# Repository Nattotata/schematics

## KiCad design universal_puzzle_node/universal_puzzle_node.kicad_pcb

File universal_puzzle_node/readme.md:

## useful links

- pinout and discussion on arduino [forum](https://forum.arduino.cc/t/esp32-c3-supermini-pinout/1189850)
- wifi debugging on arduino [forum](https://forum.arduino.cc/t/no-wifi-connect-with-esp32-c3-super-mini/1324046/25)
- potential replacement (same chip, different board) [seeedstudio wiki](https://wiki.seeedstudio.com/XIAO_ESP32C3_Getting_Started/)

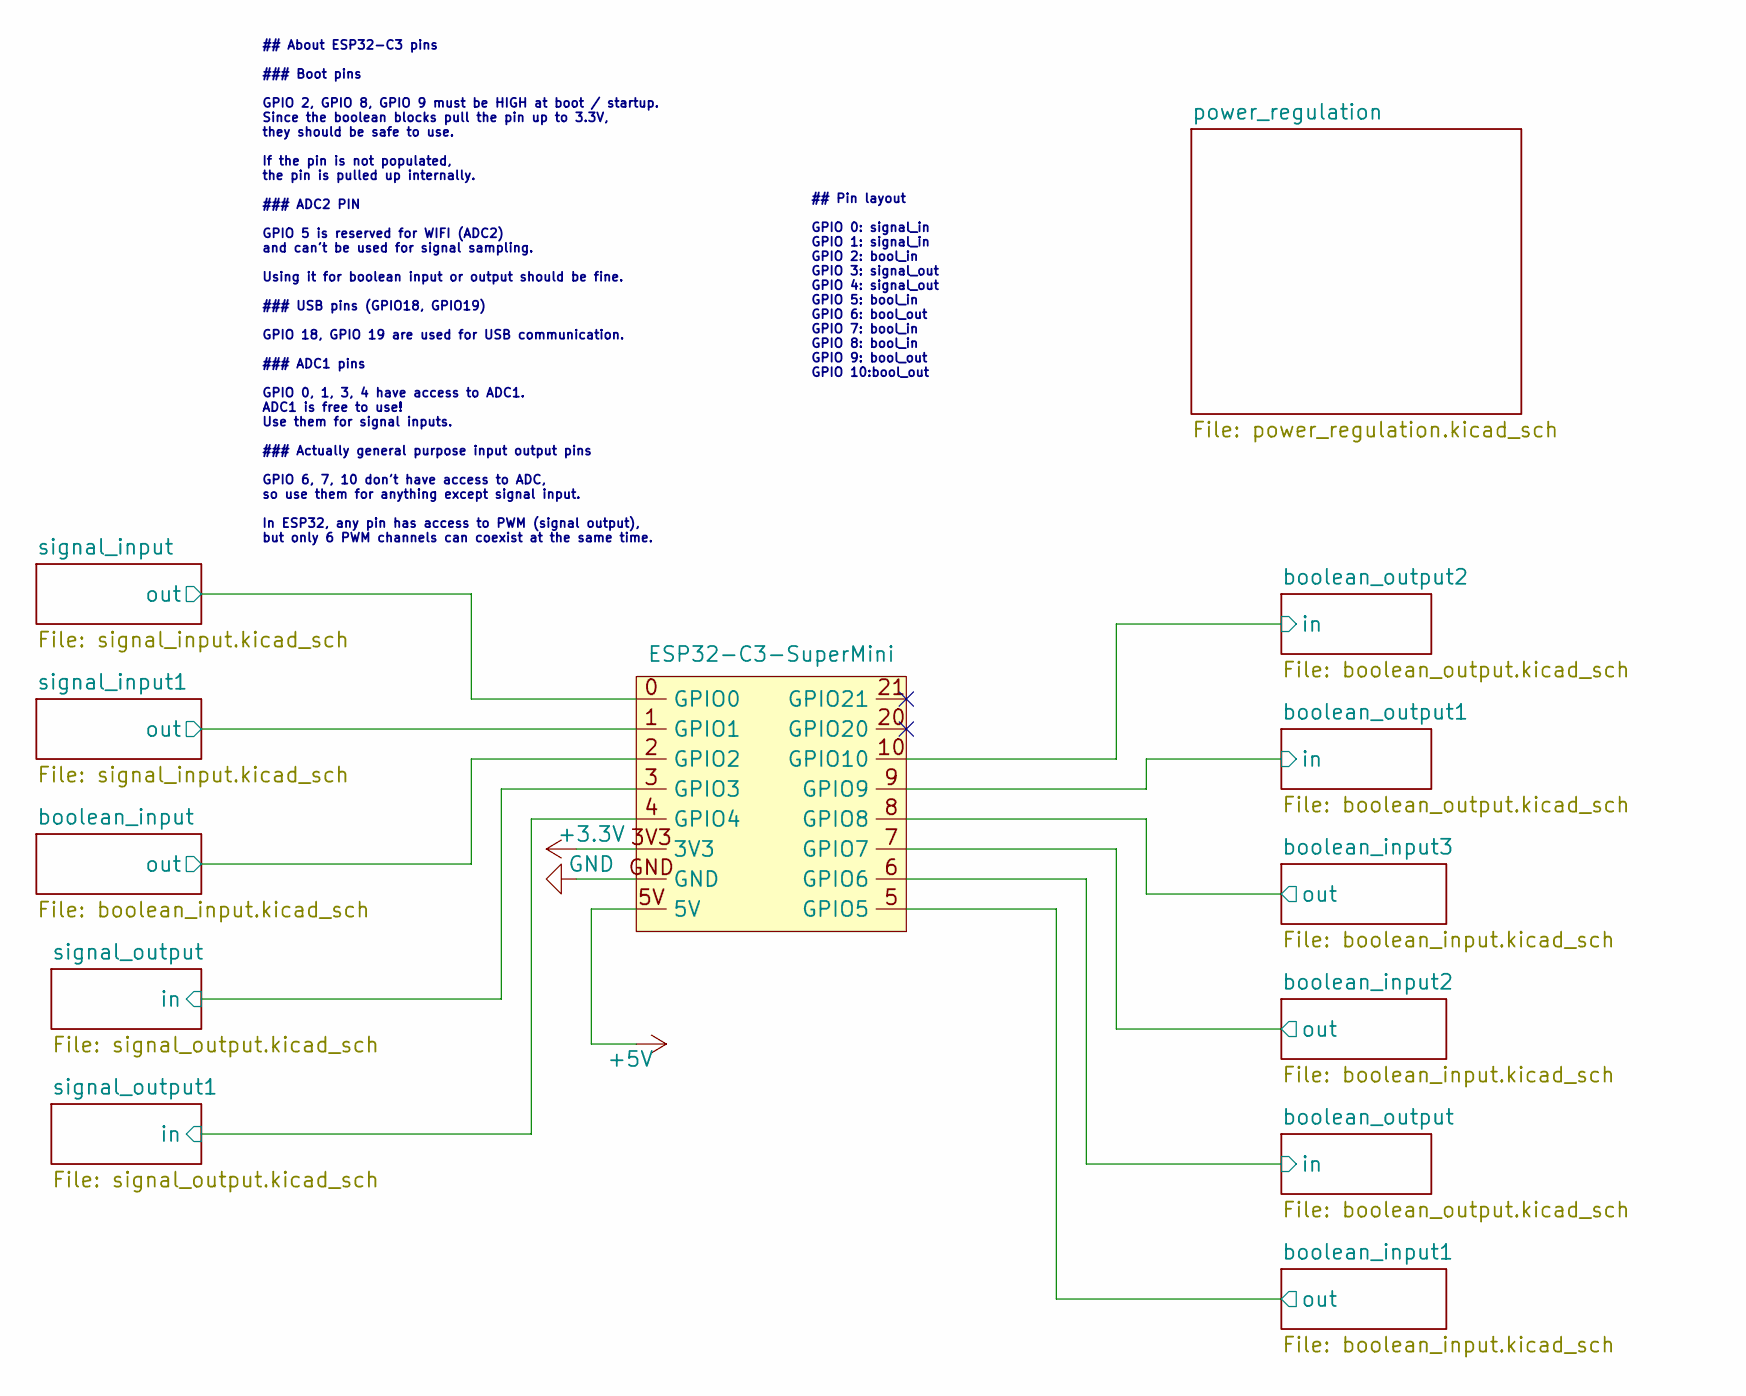
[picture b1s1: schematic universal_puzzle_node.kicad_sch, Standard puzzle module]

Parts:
U1: ESP32-C3-SuperMini

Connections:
+3.3V: U1.3V3; also elsewhere on the board
+5V: U1.5V; also elsewhere on the board
/boolean_input1/out: U1.5 (GPIO5); also elsewhere on the board
/boolean_input2/out: U1.7 (GPIO7); also elsewhere on the board
/boolean_input3/out: U1.8 (GPIO8); also elsewhere on the board
/boolean_input/out: U1.2 (GPIO2); also elsewhere on the board
/boolean_output1/in: U1.9 (GPIO9); also elsewhere on the board
/boolean_output2/in: U1.10 (GPIO10); also elsewhere on the board
/boolean_output/in: U1.6 (GPIO6); also elsewhere on the board
/signal_input1/out: U1.1 (GPIO1); also elsewhere on the board
/signal_input/out: U1.0 (GPIO0); also elsewhere on the board
/signal_output1/in: U1.4 (GPIO4); also elsewhere on the board
/signal_output/in: U1.3 (GPIO3); also elsewhere on the board
GND: U1.GND; also elsewhere on the board

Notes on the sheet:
## About ESP32-C3 pins ### Boot pins GPIO 2, GPIO 8, GPIO 9 must be HIGH at boot / startup. Since the boolean blocks pull the pin up to 3.3V, they should be safe to use. If the pin is not populated, the pin is pulled up internally. ### ADC2 PIN GPIO 5 is reserved for WIFI (ADC2) and can't be used f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
## Pin layout GPIO 0: signal_in GPIO 1: signal_in GPIO 2: bool_in GPIO 3: signal_out GPIO 4: signal_out GPIO 5: bool_in GPIO 6: bool_out GPIO 7: bool_in GPIO 8: bool_in GPIO 9: bool_out GPIO 10:bool_out

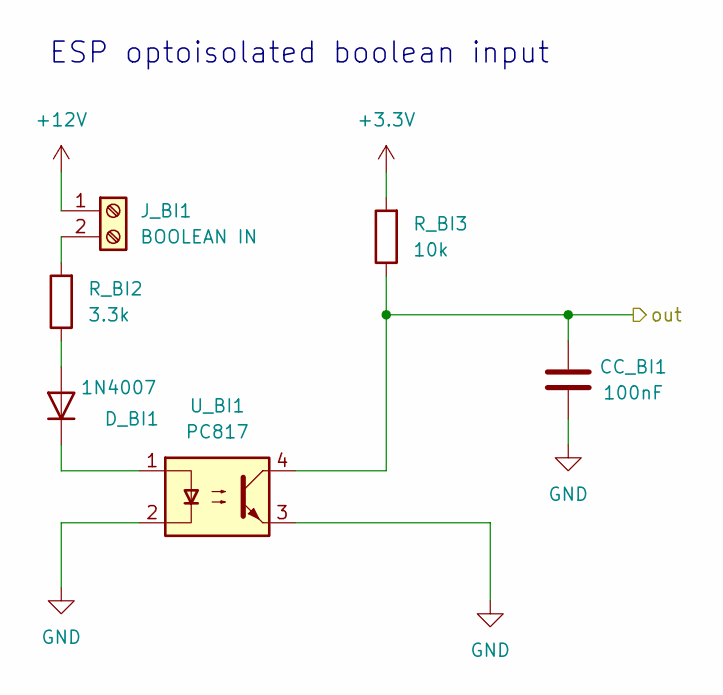
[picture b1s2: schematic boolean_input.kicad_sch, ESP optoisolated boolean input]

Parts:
CC_BI1: 100nF; C_Disc_D5.0mm_W2.5mm_P5.00mm
D_BI1: 1N4007; D_DO-41_SOD81_P10.16mm_Horizontal
J_BI1: BOOLEAN IN; TerminalBlock_Phoenix_MKDS-1,5-2-5.08_1x02_P5.08mm_Horizont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
R_BI2: 3.3k; R_Axial_DIN0207_L6.3mm_D2.5mm_P10.16mm_Horizontal
R_BI3: 10k; R_Axial_DIN0207_L6.3mm_D2.5mm_P10.16mm_Horizontal
U_BI1: PC817; DIP-4_W7.62mm

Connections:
+3.3V: R_BI3.2; also elsewhere on the board
+12V: J_BI1.1; also elsewhere on the board
/boolean_input/out: CC_BI1.1, R_BI3.1, U_BI1.4; also elsewhere on the board
GND: CC_BI1.2, U_BI1.2, U_BI1.3; also elsewhere on the board
unnamed: D_BI1.2 (A), R_BI2.1
unnamed: D_BI1.1 (K), U_BI1.1
unnamed: J_BI1.2, R_BI2.2

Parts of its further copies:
CC_BI2, CC_BI3, CC_BI4: 100nF; C_Disc_D5.0mm_W2.5mm_P5.00mm
D_BI2, D_BI3, D_BI4: 1N4007; D_DO-41_SOD81_P10.16mm_Horizontal
J_BI2, J_BI3, J_BI4: BOOLEAN IN; TerminalBlock_Phoenix_MKDS-1,5-2-5.08_1x02_P5.08mm_Horizont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
R_BI5, R_BI7, R_BI9: 3.3k; R_Axial_DIN0207_L6.3mm_D2.5mm_P10.16mm_Horizontal
R_BI6, R_BI8, R_BI10: 10k; R_Axial_DIN0207_L6.3mm_D2.5mm_P10.16mm_Horizontal
U_BI2, U_BI3, U_BI4: PC817; DIP-4_W7.62mm

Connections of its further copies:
+3.3V: R_BI6.2, R_BI8.2, R_BI10.2; also elsewhere on the board
+12V: J_BI2.1, J_BI3.1, J_BI4.1; also elsewhere on the board
/boolean_input1/out: CC_BI2.1, R_BI6.1, U_BI2.4; also elsewhere on the board
/boolean_input2/out: CC_BI3.1, R_BI8.1, U_BI3.4; also elsewhere on the board
/boolean_input3/out: CC_BI4.1, R_BI10.1, U_BI4.4; also elsewhere on the board
GND: CC_BI2.2, CC_BI3.2, CC_BI4.2, U_BI2.2, U_BI2.3, U_BI3.2, U_BI3.3, U_BI4.2, U_BI4.3; also elsewhere on the board
unnamed: D_BI2.2 (A), R_BI5.1
unnamed: D_BI2.1 (K), U_BI2.1
unnamed: D_BI3.2 (A), R_BI7.1
unnamed: D_BI3.1 (K), U_BI3.1
unnamed: D_BI4.2 (A), R_BI9.1
unnamed: D_BI4.1 (K), U_BI4.1
unnamed: J_BI2.2, R_BI5.2
unnamed: J_BI3.2, R_BI7.2
unnamed: J_BI4.2, R_BI9.2

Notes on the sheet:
ESP optoisolated boolean input

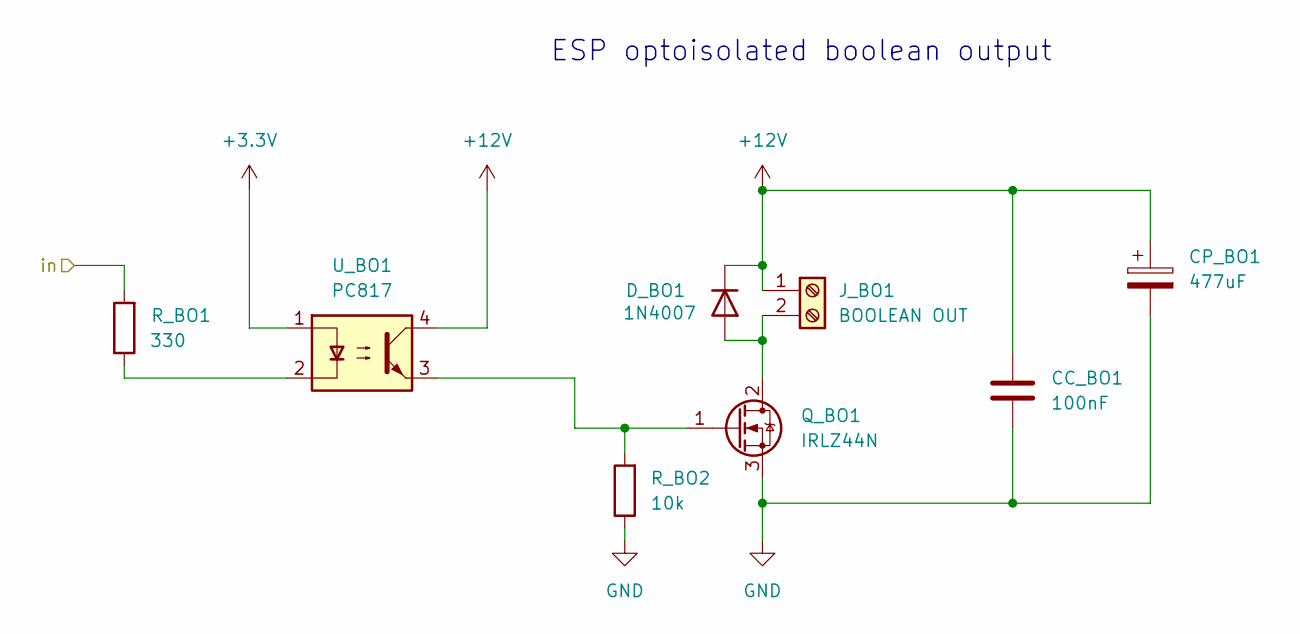
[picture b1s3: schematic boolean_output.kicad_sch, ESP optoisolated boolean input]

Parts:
CC_BO1: 100nF; C_Disc_D5.0mm_W2.5mm_P5.00mm
CP_BO1: 477uF; CP_Radial_D10.0mm_P5.00mm
D_BO1: 1N4007; D_DO-41_SOD81_P10.16mm_Horizontal
J_BO1: BOOLEAN OUT; TerminalBlock_Phoenix_MKDS-1,5-2-5.08_1x02_P5.08mm_Horizont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
Q_BO1: IRLZ44N; TO-220-3_Vertical
R_BO1: 330; R_Axial_DIN0207_L6.3mm_D2.5mm_P10.16mm_Horizontal
R_BO2: 10k; R_Axial_DIN0207_L6.3mm_D2.5mm_P10.16mm_Horizontal
U_BO1: PC817; DIP-4_W7.62mm

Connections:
+3.3V: U_BO1.1; also elsewhere on the board
+12V: CC_BO1.2, CP_BO1.1, D_BO1.1 (K), J_BO1.1, U_BO1.4; also elsewhere on the board
/boolean_output/in: R_BO1.2; also elsewhere on the board
GND: CC_BO1.1, CP_BO1.2, Q_BO1.3 (S), R_BO2.1; also elsewhere on the board
unnamed: D_BO1.2 (A), J_BO1.2, Q_BO1.2 (D)
unnamed: Q_BO1.1 (G), R_BO2.2, U_BO1.3
unnamed: R_BO1.1, U_BO1.2

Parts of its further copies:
CC_BO2, CC_BO3: 100nF; C_Disc_D5.0mm_W2.5mm_P5.00mm
CP_BO2, CP_BO3: 477uF; CP_Radial_D10.0mm_P5.00mm
D_BO2, D_BO3: 1N4007; D_DO-41_SOD81_P10.16mm_Horizontal
J_BO2, J_BO3: BOOLEAN OUT; TerminalBlock_Phoenix_MKDS-1,5-2-5.08_1x02_P5.08mm_Horizont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
Q_BO2, Q_BO3: IRLZ44N; TO-220-3_Vertical
R_BO3, R_BO5: 330; R_Axial_DIN0207_L6.3mm_D2.5mm_P10.16mm_Horizontal
R_BO4, R_BO6: 10k; R_Axial_DIN0207_L6.3mm_D2.5mm_P10.16mm_Horizontal
U_BO2, U_BO3: PC817; DIP-4_W7.62mm

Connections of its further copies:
+3.3V: U_BO2.1, U_BO3.1; also elsewhere on the board
+12V: CC_BO2.2, CC_BO3.2, CP_BO2.1, CP_BO3.1, D_BO2.1 (K), D_BO3.1 (K), J_BO2.1, J_BO3.1, U_BO2.4, U_BO3.4; also elsewhere on the board
/boolean_output1/in: R_BO3.2; also elsewhere on the board
/boolean_output2/in: R_BO5.2; also elsewhere on the board
GND: CC_BO2.1, CC_BO3.1, CP_BO2.2, CP_BO3.2, Q_BO2.3 (S), Q_BO3.3 (S), R_BO4.1, R_BO6.1; also elsewhere on the board
unnamed: D_BO2.2 (A), J_BO2.2, Q_BO2.2 (D)
unnamed: D_BO3.2 (A), J_BO3.2, Q_BO3.2 (D)
unnamed: Q_BO2.1 (G), R_BO4.2, U_BO2.3
unnamed: Q_BO3.1 (G), R_BO6.2, U_BO3.3
unnamed: R_BO3.1, U_BO2.2
unnamed: R_BO5.1, U_BO3.2

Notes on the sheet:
ESP optoisolated boolean output

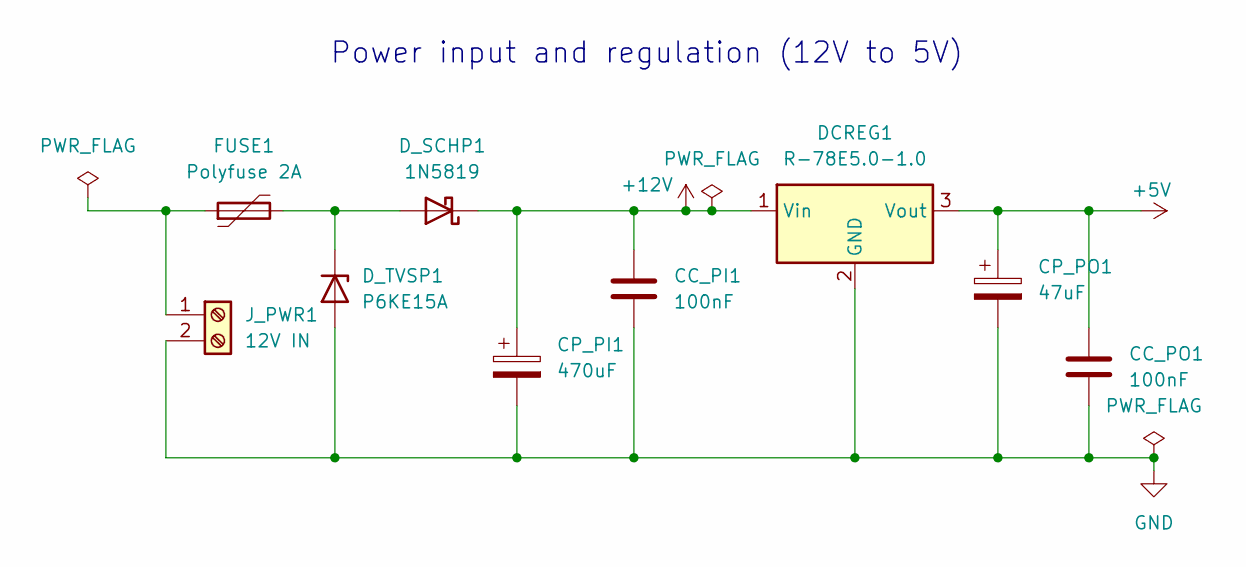
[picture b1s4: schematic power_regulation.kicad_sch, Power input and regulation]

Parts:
CC_PI1: 100nF; C_Disc_D5.0mm_W2.5mm_P5.00mm
CC_PO1: 100nF; C_Disc_D5.0mm_W2.5mm_P5.00mm
CP_PI1: 470uF; CP_Radial_D10.0mm_P5.00mm
CP_PO1: 47uF; CP_Radial_D6.3mm_P2.50mm
DCREG1: R-78E5.0-1.0; Converter_DCDC_RECOM_R-78E-0.5_THT
D_SCHP1: 1N5819; D_DO-35_SOD27_P7.62mm_Horizontal
D_TVSP1: P6KE15A; D_DO-15_P12.70mm_Horizontal
FUSE1: Polyfuse 2A; Fuse_BelFuse_0ZRE0040FF_L11.5mm_W3.8mm
J_PWR1: 12V IN; TerminalBlock_Phoenix_MKDS-1,5-2-5.08_1x02_P5.08mm_Horizont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

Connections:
+5V: CC_PO1.1, CP_PO1.1, DCREG1.3 (Vout); also elsewhere on the board
+12V: CC_PI1.1, CP_PI1.1, DCREG1.1 (Vin), D_SCHP1.1 (K); also elsewhere on the board
GND: CC_PI1.2, CC_PO1.2, CP_PI1.2, CP_PO1.2, DCREG1.2 (GND), D_TVSP1.2 (A), J_PWR1.2; also elsewhere on the board
unnamed: D_SCHP1.2 (A), D_TVSP1.1 (K), FUSE1.2
unnamed: FUSE1.1, J_PWR1.1

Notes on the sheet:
Power input and regulation (12V to 5V)

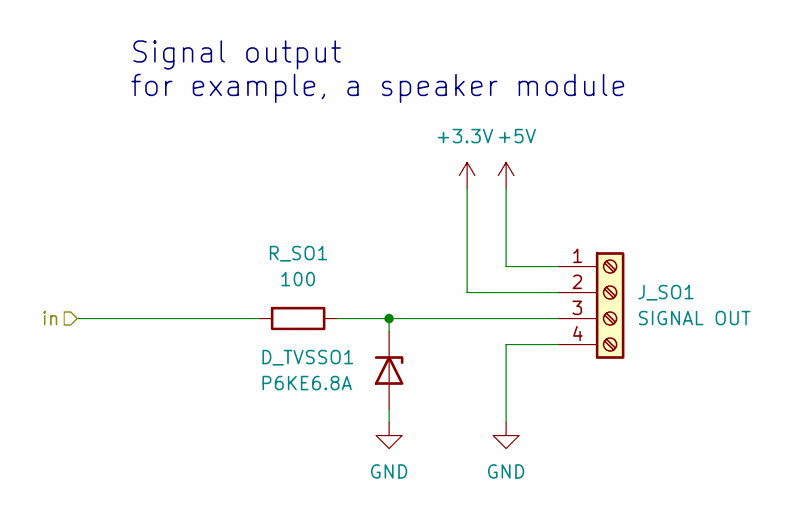
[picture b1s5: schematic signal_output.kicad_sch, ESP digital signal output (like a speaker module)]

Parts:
D_TVSSO1: P6KE6.8A; D_DO-15_P12.70mm_Horizontal
J_SO1: SIGNAL OUT; TerminalBlock_Phoenix_MKDS-1,5-4-5.08_1x04_P5.08mm_Horizont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
R_SO1: 100; R_Axial_DIN0207_L6.3mm_D2.5mm_P10.16mm_Horizontal

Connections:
+3.3V: J_SO1.2; also elsewhere on the board
+5V: J_SO1.1; also elsewhere on the board
/signal_output/in: R_SO1.2; also elsewhere on the board
GND: D_TVSSO1.2 (A), J_SO1.4; also elsewhere on the board
unnamed: D_TVSSO1.1 (K), J_SO1.3, R_SO1.1

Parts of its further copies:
D_TVSSO2: P6KE6.8A; D_DO-15_P12.70mm_Horizontal
J_SO2: SIGNAL OUT; TerminalBlock_Phoenix_MKDS-1,5-4-5.08_1x04_P5.08mm_Horizont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
R_SO4: 100; R_Axial_DIN0207_L6.3mm_D2.5mm_P10.16mm_Horizontal

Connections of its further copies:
+3.3V: J_SO2.2; also elsewhere on the board
+5V: J_SO2.1; also elsewhere on the board
/signal_output1/in: R_SO4.2; also elsewhere on the board
GND: D_TVSSO2.2 (A), J_SO2.4; also elsewhere on the board
unnamed: D_TVSSO2.1 (K), J_SO2.3, R_SO4.1

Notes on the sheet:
Signal output for example, a speaker module

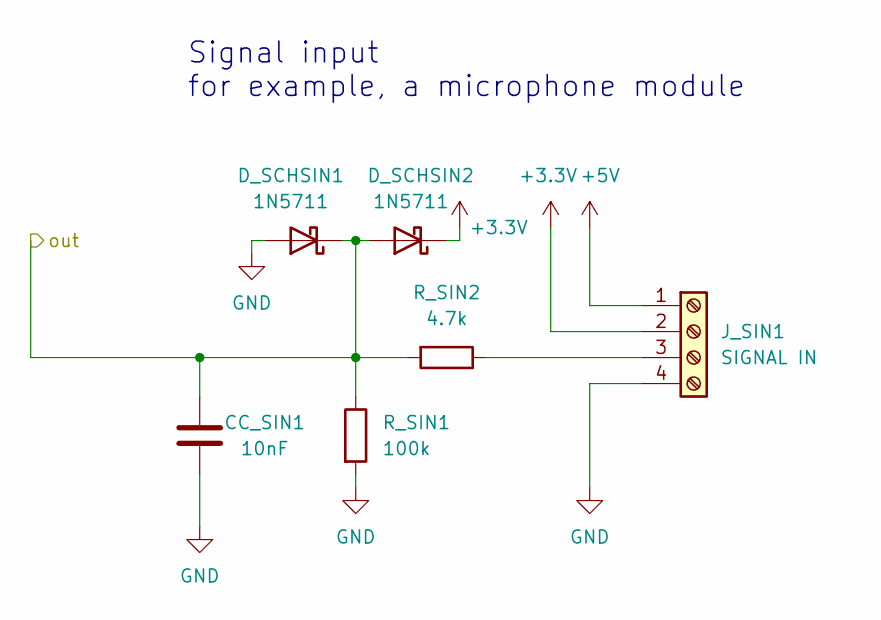
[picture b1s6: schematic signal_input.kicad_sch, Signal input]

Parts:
CC_SIN1: 10nF; C_Disc_D5.0mm_W2.5mm_P5.00mm
D_SCHSIN1, D_SCHSIN2: 1N5711; D_DO-35_SOD27_P7.62mm_Horizontal
J_SIN1: SIGNAL IN; TerminalBlock_Phoenix_MKDS-1,5-4-5.08_1x04_P5.08mm_Horizont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
R_SIN1: 100k; R_Axial_DIN0207_L6.3mm_D2.5mm_P10.16mm_Horizontal
R_SIN2: 4.7k; R_Axial_DIN0207_L6.3mm_D2.5mm_P10.16mm_Horizontal

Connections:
+3.3V: D_SCHSIN2.1 (K), J_SIN1.2; also elsewhere on the board
+5V: J_SIN1.1; also elsewhere on the board
/signal_input/out: CC_SIN1.1, R_SIN1.1, R_SIN2.2; also elsewhere on the board
GND: CC_SIN1.2, D_SCHSIN1.2 (A), J_SIN1.4, R_SIN1.2; also elsewhere on the board
unnamed: J_SIN1.3, R_SIN2.1

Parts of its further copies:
CC_SIN2: 10nF; C_Disc_D5.0mm_W2.5mm_P5.00mm
J_SIN2: SIGNAL IN; TerminalBlock_Phoenix_MKDS-1,5-4-5.08_1x04_P5.08mm_Horizont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
R_SIN3: 100k; R_Axial_DIN0207_L6.3mm_D2.5mm_P10.16mm_Horizontal
R_SIN4: 4.7k; R_Axial_DIN0207_L6.3mm_D2.5mm_P10.16mm_Horizontal

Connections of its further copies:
+3.3V: J_SIN2.2; also elsewhere on the board
+5V: J_SIN2.1; also elsewhere on the board
/signal_input1/out: CC_SIN2.1, R_SIN3.1, R_SIN4.2; also elsewhere on the board
GND: CC_SIN2.2, J_SIN2.4, R_SIN3.2; also elsewhere on the board
unnamed: J_SIN2.3, R_SIN4.1

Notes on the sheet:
Signal input for example, a microphone module

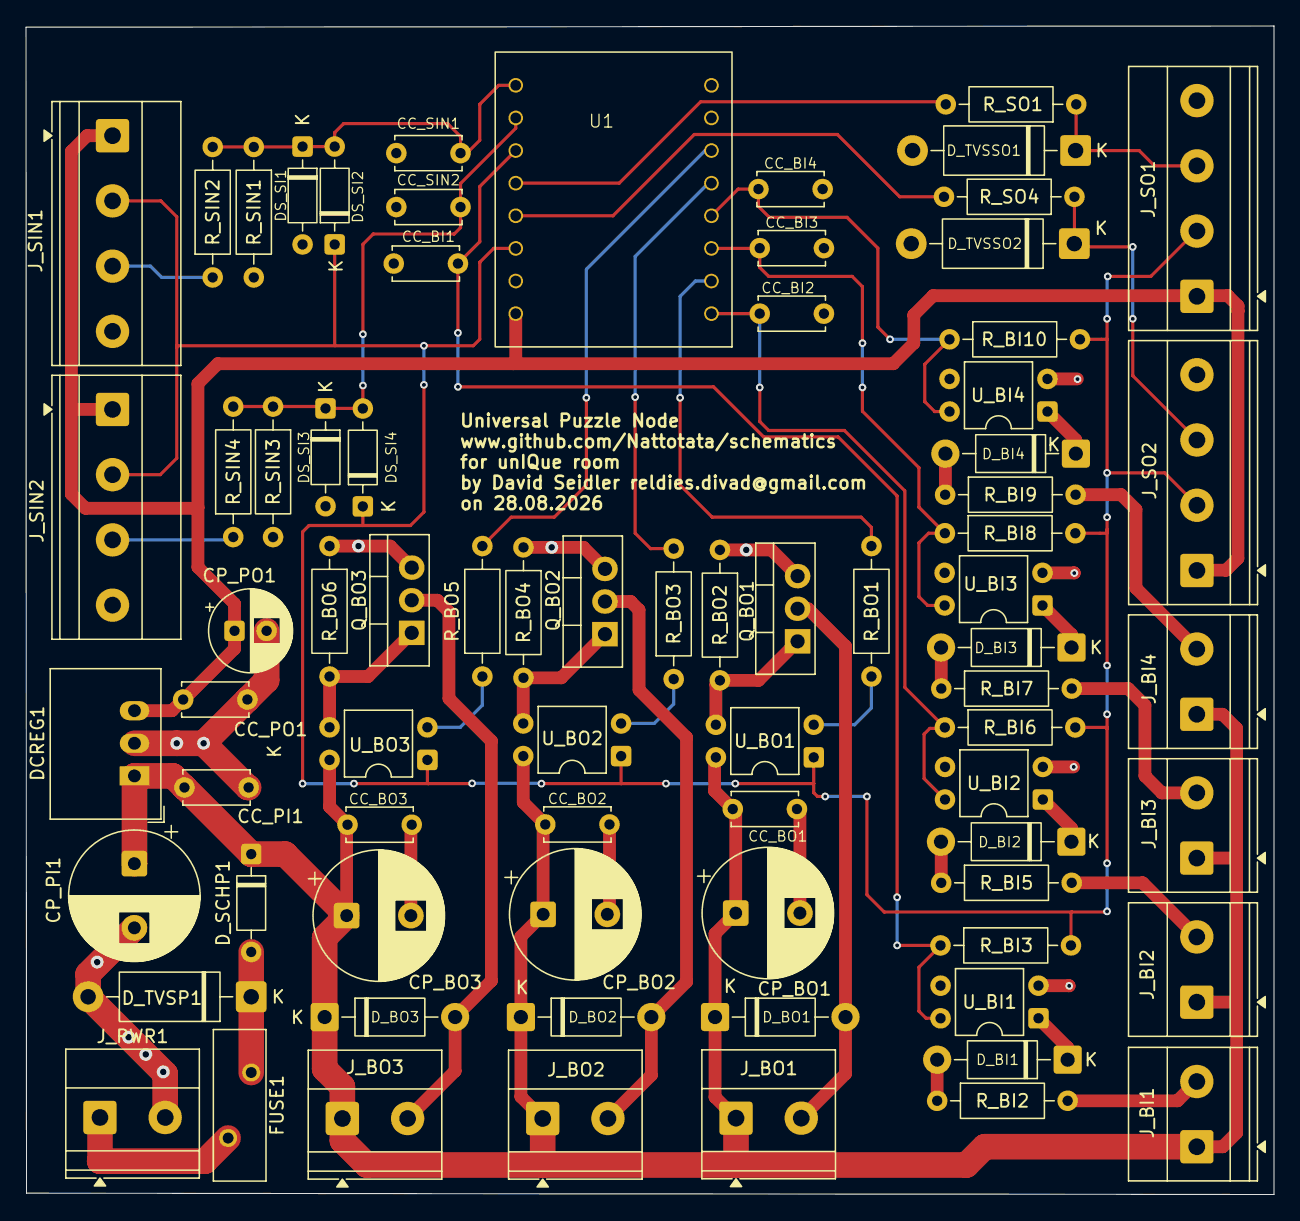
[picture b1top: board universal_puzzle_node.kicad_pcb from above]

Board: 2 copper layers, 97.2 x 91.0 mm, 76 parts (0 on the bottom side), 42 nets.

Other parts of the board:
DS_SI1, DS_SI2, DS_SI3, DS_SI4: 1N5711; D_DO-35_SOD27_P7.62mm_Horizontal

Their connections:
+3.3V: DS_SI2.1 (K), DS_SI4.1 (K); also elsewhere on the board
/signal_input1/out: DS_SI3.1 (K), DS_SI4.2 (A); also elsewhere on the board
/signal_input/out: DS_SI1.1 (K), DS_SI2.2 (A); also elsewhere on the board
GND: DS_SI1.2 (A), DS_SI3.2 (A); also elsewhere on the board

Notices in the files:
universal_puzzle_node/universal_puzzle_node.kicad_pcb:
Licensed under CC-BY-SA 4.0
